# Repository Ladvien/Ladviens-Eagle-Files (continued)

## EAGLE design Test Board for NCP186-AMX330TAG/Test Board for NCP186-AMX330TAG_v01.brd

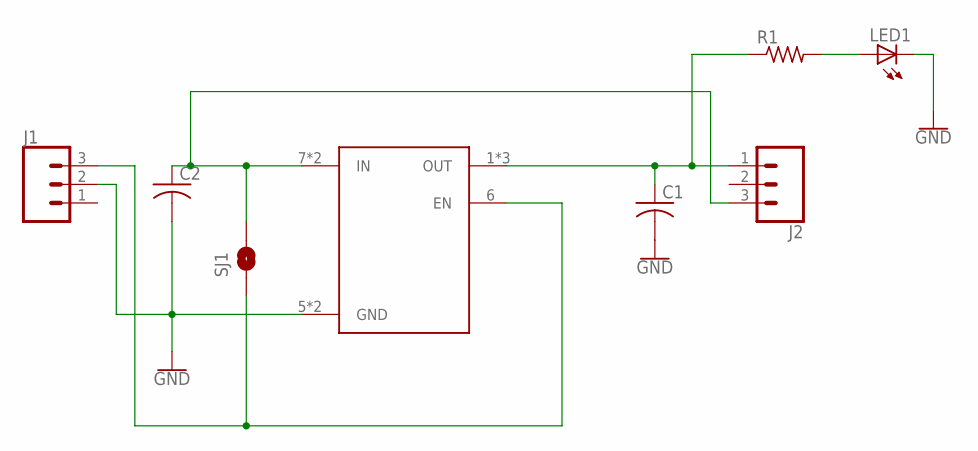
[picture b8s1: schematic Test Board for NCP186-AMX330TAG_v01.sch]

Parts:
C1, C2: C-USC0805K; C0805K
J1, J2: CONN_03; 1X03
LED1: LEDCHIPLED_0603; CHIPLED_0603
R1: R-US_R0805W; R0805W
SJ1: SOLDERJUMPERNO; SJ_2S-NO
U$1: NCP186-AMX330TAG; XDFN8

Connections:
EN: J1.3, SJ1.1, U$1.6 (EN)
GND: C1.2, C2.2, J1.2, LED1.C, U$1.5 (GND), U$1.PAD (GND)
IIN: C2.1, J2.3, SJ1.2, U$1.7 (IN), U$1.8 (IN)
unnamed: LED1.A, R1.2
OUT: C1.1, J2.1, R1.1, U$1.1 (OUT), U$1.2 (OUT), U$1.4 (OUT)

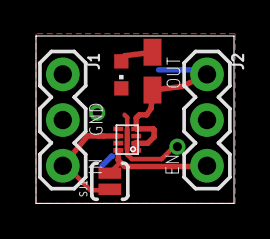
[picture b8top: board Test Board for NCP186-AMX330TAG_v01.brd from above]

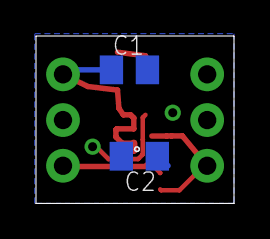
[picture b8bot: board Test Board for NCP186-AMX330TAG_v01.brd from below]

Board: 2 copper layers, 10.9 x 9.2 mm, 8 parts (2 on the bottom side), 5 nets.

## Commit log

2016-01-08 Here we go!
2016-01-08 Added work computer PCB doodles
2016-01-08 Added my part library
2016-01-08 SMD'ing the LAB Led Controller
2016-01-08 Working
2016-01-10 Working on Lab LED
2016-01-11 Lab Controller
2016-02-22 Adding temp probe, UART, fan, I2C
2016-02-28 Added ESP-07, RX/TX level converter, temp probe connection. Cleaned silkscreen
2016-02-28 Finished?
2016-04-18 BoB Board
2016-04-18 Added servo / digital power rails
2016-04-24 Added Robinson board
2016-04-26 Finished Robinson schematic
2016-05-04 Routing Robinson Board
2016-05-05 Working on BoB Board
2016-05-06 Routing BoB board
2016-05-07 Finished routing BoB Board
2016-05-07 Finished BoB Brain Board
2016-05-07 Order BoB Brain Board v05
2017-01-11 ROBBER V01
2017-02-06 Robber and Test NCP186
2017-02-12 Updated NCP part
2017-02-17 Added UART_Splitter
2017-02-19 UART Splitter
2017-02-24 Working on UART Splitter
2017-03-03 UART
2017-12-24 Added Robber v.2 and Micro Stepper
2017-12-29 Updated TinyKey AVR ISP
2017-12-29 Reworked Attiny10
2017-12-30 Add DRV8835
2017-12-31 Micro driver
2018-01-03 MicroStepper
2018-02-12 Refactored ADUM1250ARZ
2018-05-12 rp0w i2c board
